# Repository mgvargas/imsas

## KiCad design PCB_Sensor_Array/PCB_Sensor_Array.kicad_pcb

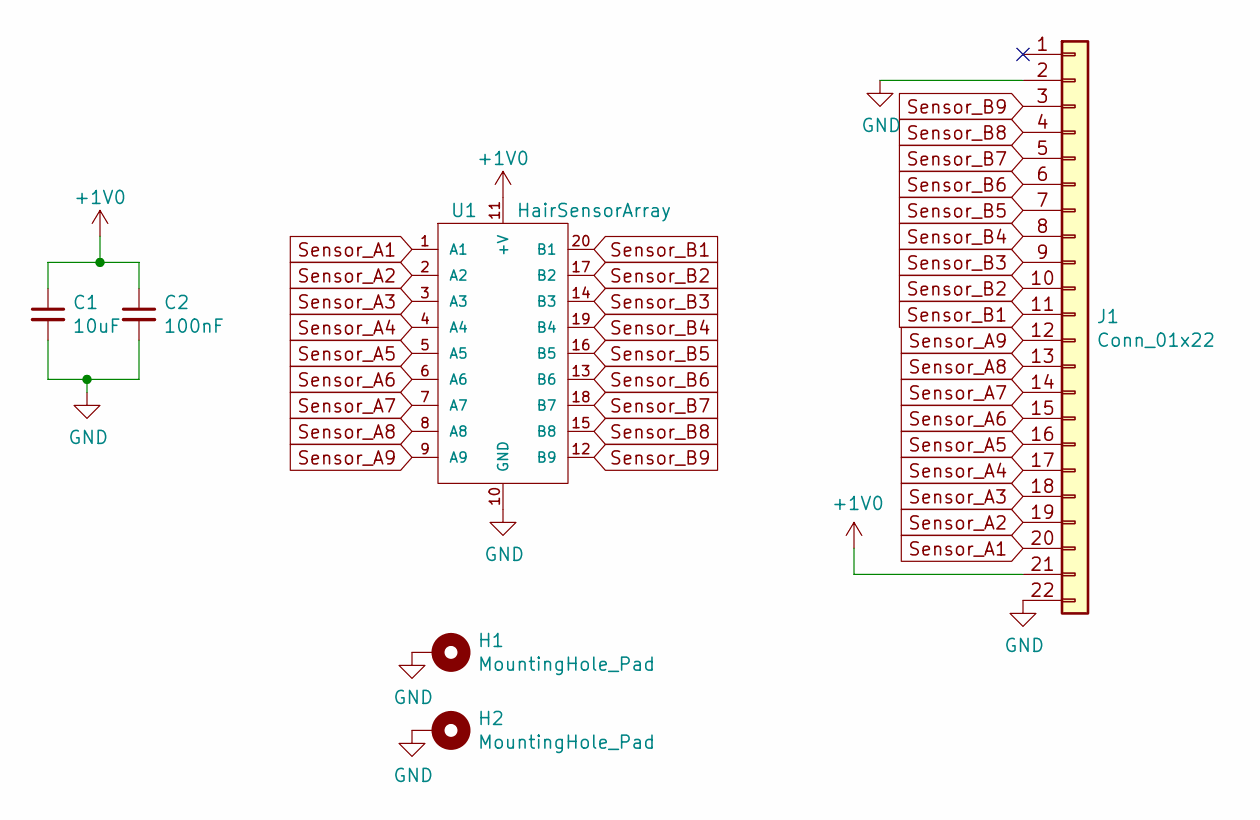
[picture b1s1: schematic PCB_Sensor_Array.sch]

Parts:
C1: 10uF; C_0603_1608Metric
C2: 100nF; C_0603_1608Metric
H1, H2: MountingHole_Pad; MountingHole_3.2mm_M3_Pad_Via
J1: Conn_01x22; Molex_200528-0220_1x22-1MP_P1.00mm_Horizontal
U1: HairSensorArray; Hair_Sensor_QFP-20_10x10_Pitch0.5mm

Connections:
+1V0: C1.1, C2.1, J1.21, U1.11 (+V)
GND: C1.2, C2.2, H1.1, H2.1, J1.2, J1.22, U1.10 (GND)
Sensor_A1: J1.20, U1.1 (A1)
Sensor_A2: J1.19, U1.2 (A2)
Sensor_A3: J1.18, U1.3 (A3)
Sensor_A4: J1.17, U1.4 (A4)
Sensor_A5: J1.16, U1.5 (A5)
Sensor_A6: J1.15, U1.6 (A6)
Sensor_A7: J1.14, U1.7 (A7)
Sensor_A8: J1.13, U1.8 (A8)
Sensor_A9: J1.12, U1.9 (A9)
Sensor_B1: J1.11, U1.20 (B1)
Sensor_B2: J1.10, U1.17 (B2)
Sensor_B3: J1.9, U1.14 (B3)
Sensor_B4: J1.8, U1.19 (B4)
Sensor_B5: J1.7, U1.16 (B5)
Sensor_B6: J1.6, U1.13 (B6)
Sensor_B7: J1.5, U1.18 (B7)
Sensor_B8: J1.4, U1.15 (B8)
Sensor_B9: J1.3, U1.12 (B9)

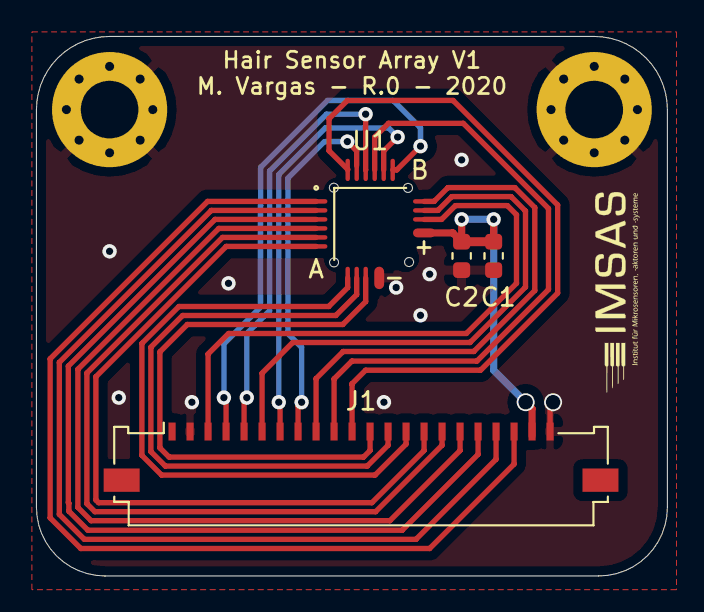
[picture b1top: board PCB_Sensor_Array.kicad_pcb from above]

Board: 2 copper layers, 35.1 x 30.0 mm, 6 parts (0 on the bottom side), 20 nets.

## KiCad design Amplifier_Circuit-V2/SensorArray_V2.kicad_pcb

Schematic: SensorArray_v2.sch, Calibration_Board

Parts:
C1: 10u; C_0805_2012Metric
C2, C3, C4, C5, C6, C7, C8, C9, C10: 100n; C_0402_1005Metric
C11, C12: 2.2u; C_0603_1608Metric
C13, C14: 12p; C_0402_1005Metric
D1, D6: LED; LED_0603_1608Metric
H1, H2, H3, H4: MountingHole_Pad; MountingHole_4.3mm_M4_Pad_Via
HSE1: 16MHz; Crystal_SMD_3225-4Pin_3.2x2.5mm
J1: UART_Connector; PinSocket_1x02_P2.54mm_Vertical
J2: Conn_02x05_Odd_Even; PinHeader_2x05_P1.27mm_Vertical_SMD
J3: I2C_Connector; PinHeader_1x02_P2.54mm_Vertical
J4: VCC_Connector; PinHeader_1x02_P2.54mm_Vertical
J5: SPI1_Connector; PinHeader_1x04_P2.54mm_Vertical
J6: 3V3_Connector; PinHeader_1x02_P2.54mm_Vertical
J10: SPI2_Connector; PinHeader_1x04_P2.54mm_Vertical
J11: USB_B_Micro; USB_Micro-B_Molex-105133-0001
R1, R2, R6, R19: 2k2; R_0603_1608Metric
R3, R4: 10k; R_0603_1608Metric
R5: 220; R_0603_1608Metric
R20: 1.5k; R_0603_1608Metric
S1: 1825910-6; SMD-4_5x4.4mm_P4mm; MPN 1825910-6; Digi-Key_PN 450-1650-ND
SW1: SW_DIP_x01; SW_DIP_SPSTx01_Slide_9.78x4.72mm_W7.62mm_P2.54mm
U1: STM32F405RGTx; LQFP-64_10x10mm_P0.5mm
U11: USBLC6-2SC6; SOT-23-6

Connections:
+3.3VA: U1.13 (VDDA); also elsewhere on the board
+3V3: C1.1, C2.1, C3.1, C4.1, C5.1, C6.1, C7.1, C8.1, C9.1, C10.1, J2.1, J6.1, R1.2, R2.2, R19.2, R20.1, U1.1 (VBAT), U1.19 (VDD), U1.32 (VDD), U1.48 (VDD), U1.64 (VDD); also elsewhere on the board
ADC_SPI2_CS: J10.1, U1.17 (PA3); also elsewhere on the board
AMP_OUT_A: U1.15 (PA1); also elsewhere on the board
AMP_OUT_B: U1.16 (PA2); also elsewhere on the board
BOOT0: R3.1, U1.60 (BOOT0)
BOOT1: R4.1, U1.28 (PB2)
GND: C1.2, C2.2, C3.2, C4.2, C5.2, C6.2, C7.2, C8.2, C9.2, C10.2, C11.2, C12.2, C13.2, C14.2, H1.1, H2.1, H3.1, H4.1, HSE1.2, HSE1.4, J2.3, J2.5, J2.9, J4.2, J6.2, J11.5, R3.2, R4.2, R6.1, SW1.1, U1.18 (VSS), U1.63 (VSS), U11.2; also elsewhere on the board
GNDA: U1.12 (VSSA); also elsewhere on the board
HSE_IN: C13.1, HSE1.1, U1.5 (PH0)
HSE_OUT: R5.1, U1.6 (PH1)
I2C1_SCL: J3.2, R1.1, U1.58 (PB6)
I2C1_SDA: J3.1, R2.1, U1.59 (PB7)
MUXA_S0: U1.8 (PC0); also elsewhere on the board
MUXA_S1: U1.9 (PC1); also elsewhere on the board
MUXA_S2: U1.10 (PC2); also elsewhere on the board
MUXA_S3: U1.11 (PC3); also elsewhere on the board
MUXB_S0: U1.24 (PC4); also elsewhere on the board
MUXB_S1: U1.25 (PC5); also elsewhere on the board
MUXB_S2: U1.37 (PC6); also elsewhere on the board
MUXB_S3: U1.38 (PC7); also elsewhere on the board
NRST: J2.10, U1.7 (NRST)
unnamed: C11.1, U1.31 (VCAP_1)
unnamed: C12.1, U1.47 (VCAP_2)
unnamed: C14.1, HSE1.3, R5.2
unnamed: D1.1 (K), R6.2
unnamed: D1.2 (A), U1.33 (PB12)
unnamed: D6.2 (A), R20.2
PushButton_Calibration: S1.3, U1.39 (PC8)
PushButton_VDD: R19.1, S1.1
SPI1_CS: J5.1, U1.20 (PA4)
SPI1_CS_POTIA: U1.26 (PB0); also elsewhere on the board
SPI1_CS_POTIB: U1.27 (PB1); also elsewhere on the board
SPI1_MISO: J5.3, U1.22 (PA6); also elsewhere on the board
SPI1_MOSI: J5.4, U1.23 (PA7); also elsewhere on the board
SPI1_SCK: J5.2, U1.21 (PA5); also elsewhere on the board
SPI2_MISO: J10.3, U1.35 (PB14); also elsewhere on the board
SPI2_MOSI: J10.4, U1.36 (PB15); also elsewhere on the board
SPI2_SCK: J10.2, U1.29 (PB10); also elsewhere on the board
SWCLK: J2.4, U1.49 (PA14)
SWDIO: J2.2, U1.46 (PA13)
SWO: J2.6, U1.55 (PB3)
Switch_Mode: D6.1 (K), SW1.2, U1.40 (PC9)
USART1_RX: J1.2, U1.43 (PA10)
USART1_TX: J1.1, U1.42 (PA9)
USB_CONN_D+: J11.3, U11.3
USB_CONN_D-: J11.2, U11.1
USB_D+: U1.45 (PA12), U11.4
USB_D-: U1.44 (PA11), U11.6

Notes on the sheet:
Cl = 2x (CLoad_CRYSTAL - CPARASITIC) Cl = 2 x (9p - 3p)
I2C Pull resistors
Crystal
USB with ESD protection

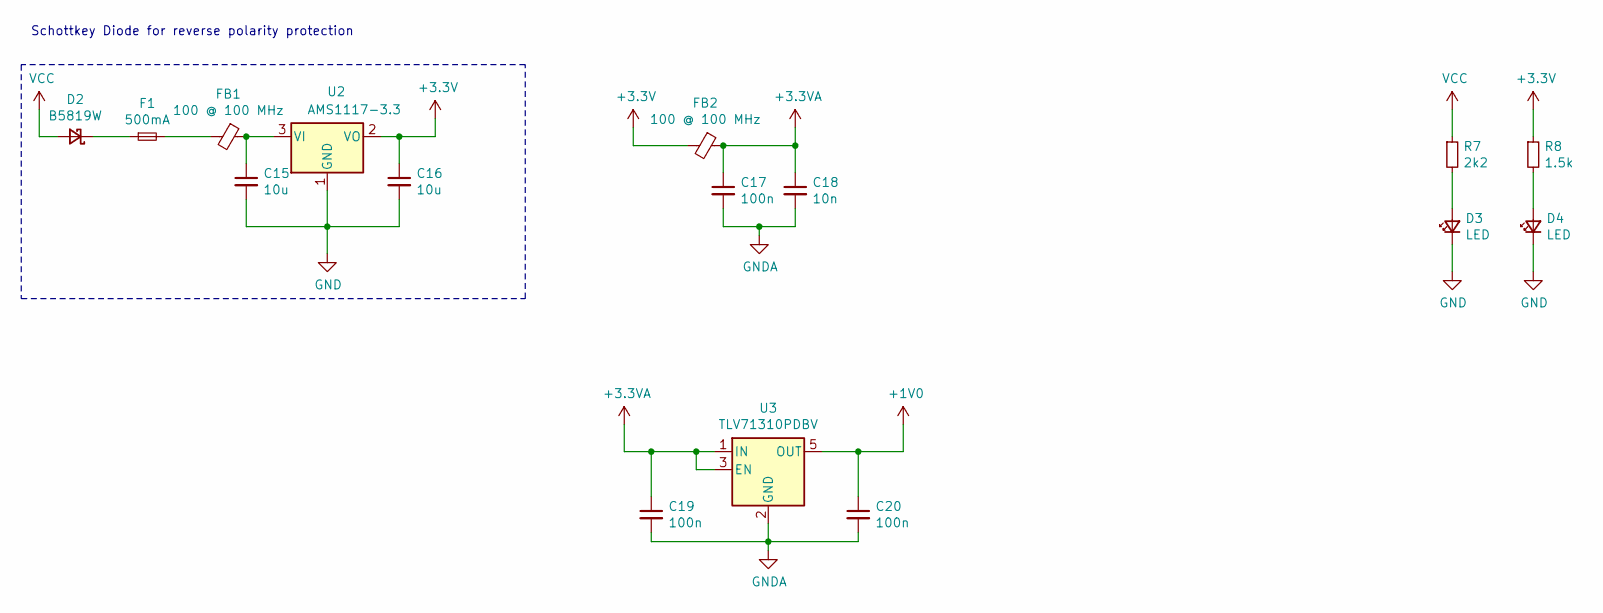
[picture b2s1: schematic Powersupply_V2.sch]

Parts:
C15, C16: 10u; C_0805_2012Metric
C17, C19, C20: 100n; C_0402_1005Metric
C18: 10n; C_0402_1005Metric
D2: B5819W; D_SOD-123
D3, D4: LED; LED_0603_1608Metric
F1: 500mA; Fuse_0603_1608Metric
FB1, FB2: 100 @ 100 MHz; L_0805_2012Metric
R7: 2k2; R_0603_1608Metric
R8: 1.5k; R_0603_1608Metric
U2: AMS1117-3.3; SOT-223-3_TabPin2
U3: TLV71310PDBV; SOT-23-5

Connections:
+1V0: C20.1, U3.5 (OUT); also elsewhere on the board
+3.3VA: C17.1, C18.1, C19.1, FB2.1, U3.1 (IN), U3.3 (EN); also elsewhere on the board
+3V3: C16.1, FB2.2, R8.1, U2.2 (VO); also elsewhere on the board
GND: C15.2, C16.2, D3.1 (K), D4.1 (K), U2.1 (GND); also elsewhere on the board
GNDA: C17.2, C18.2, C19.2, C20.2, U3.2 (GND); also elsewhere on the board
unnamed: C15.1, FB1.1, U2.3 (VI)
unnamed: D3.2 (A), R7.2
unnamed: D4.2 (A), R8.2

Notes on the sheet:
Schottkey Diode for reverse polarity protection

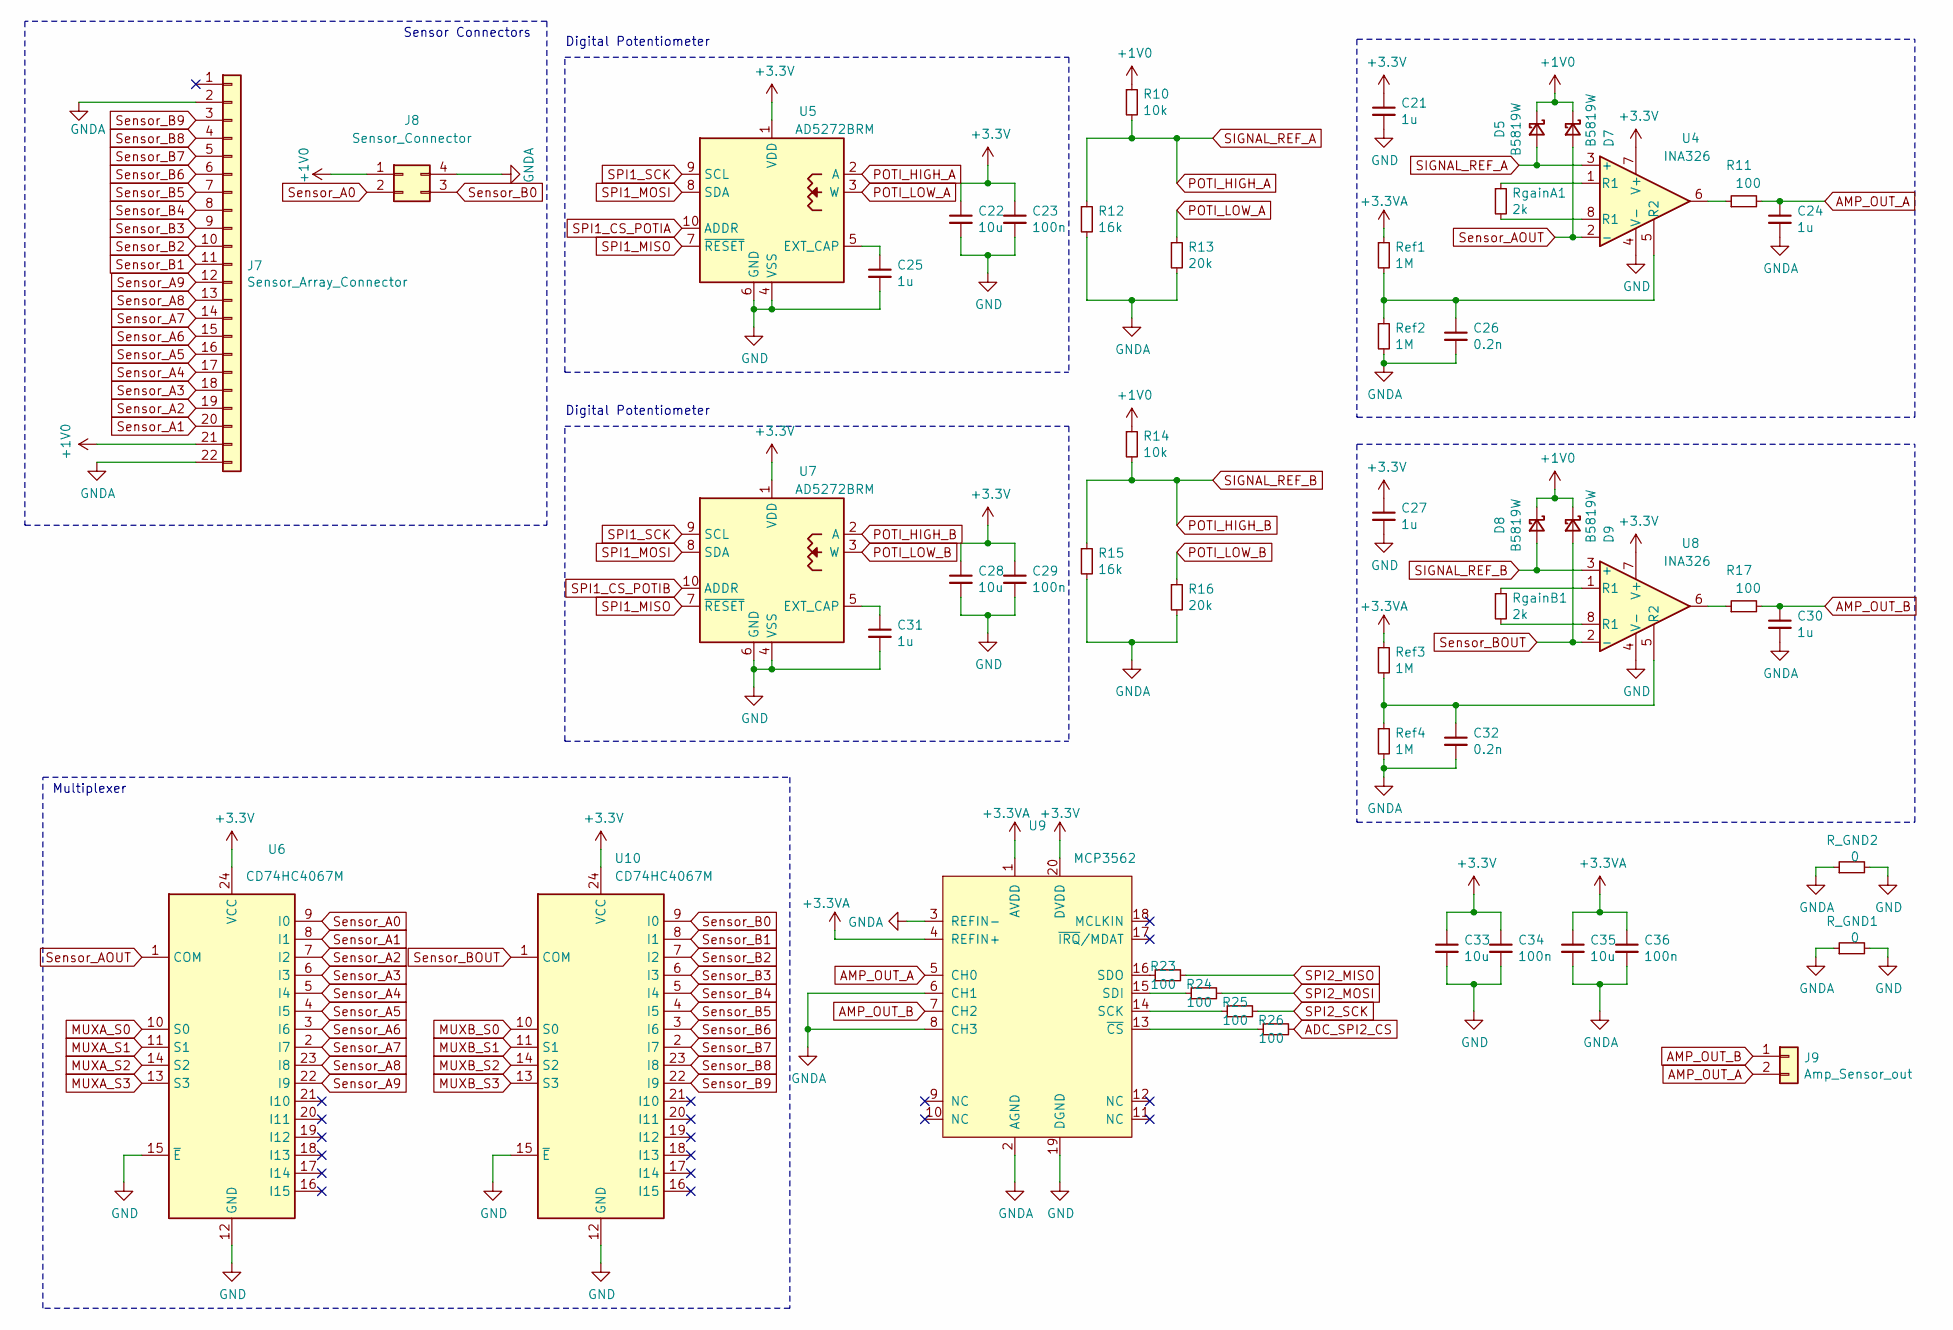
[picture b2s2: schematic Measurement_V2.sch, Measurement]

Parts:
C21, C24, C25, C27, C30, C31: 1u; C_0603_1608Metric
C22, C28, C33, C35: 10u; C_0805_2012Metric
C23, C29, C34, C36: 100n; C_0402_1005Metric
C26, C32: 0.2n; C_0603_1608Metric
D5, D7, D8, D9: B5819W; D_SOD-123
J7: Sensor_Array_Connector; Molex_200528-0220_1x22-1MP_P1.00mm_Horizontal
J8: Sensor_Connector; PinHeader_2x02_P2.54mm_Vertical
J9: Amp_Sensor_out; PinHeader_1x02_P2.54mm_Vertical
R10, R14: 10k; R_0603_1608Metric
R11, R17: 100; R_0603_1608Metric
R12, R15: 16k; R_0603_1608Metric
R13, R16: 20k; R_0603_1608Metric
R23, R24, R25, R26: 100; R_0402_1005Metric
R_GND1, R_GND2: 0; R_0603_1608Metric
Ref1, Ref2, Ref3, Ref4: 1M; R_0603_1608Metric
RgainA1: 2k; R_0603_1608Metric
RgainB1: 2k; R_0603_1608Metric
U4, U8: INA326; MSOP-8_3x3mm_P0.65mm
U5, U7: AD5272BRM; MSOP-10_3x3mm_P0.5mm
U6, U10: CD74HC4067M; SOIC-24W_7.5x15.4mm_P1.27mm
U9: MCP3562; TSSOP-20_W4.4mm

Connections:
+1V0: D5.1 (K), D7.1 (K), D8.1 (K), D9.1 (K), J7.21, J8.1, R10.1, R14.1; also elsewhere on the board
+3.3VA: C35.1, C36.1, Ref1.1, Ref3.1, U9.1 (AVDD), U9.4 (REFIN+); also elsewhere on the board
+3V3: C21.1, C22.1, C23.1, C27.1, C28.1, C29.1, C33.1, C34.1, U4.7 (V+), U5.1 (VDD), U6.24 (VCC), U7.1 (VDD), U8.7 (V+), U9.20 (DVDD), U10.24 (VCC); also elsewhere on the board
ADC_SPI2_CS: R26.2; also elsewhere on the board
AMP_OUT_A: C24.1, J9.2, R11.2, U9.5 (CH0); also elsewhere on the board
AMP_OUT_B: C30.1, J9.1, R17.2, U9.7 (CH2); also elsewhere on the board
GND: C21.2, C22.2, C23.2, C25.2, C27.2, C28.2, C29.2, C31.2, C33.2, C34.2, R_GND1.2, R_GND2.2, U4.4 (V-), U5.4 (VSS), U5.6 (GND), U6.12 (GND), U6.15 (~E), U7.4 (VSS), U7.6 (GND), U8.4 (V-), U9.19 (DGND), U10.12 (GND), U10.15 (~E); also elsewhere on the board
GNDA: C24.2, C26.2, C30.2, C32.2, C35.2, C36.2, J7.2, J7.22, J8.4, R12.2, R13.2, R15.2, R16.2, R_GND1.1, R_GND2.1, Ref2.2, Ref4.2, U9.2 (AGND), U9.3 (REFIN-), U9.6 (CH1), U9.8 (CH3); also elsewhere on the board
MUXA_S0: U6.10 (S0); also elsewhere on the board
MUXA_S1: U6.11 (S1); also elsewhere on the board
MUXA_S2: U6.14 (S2); also elsewhere on the board
MUXA_S3: U6.13 (S3); also elsewhere on the board
MUXB_S0: U10.10 (S0); also elsewhere on the board
MUXB_S1: U10.11 (S1); also elsewhere on the board
MUXB_S2: U10.14 (S2); also elsewhere on the board
MUXB_S3: U10.13 (S3); also elsewhere on the board
unnamed: C25.1, U5.5 (EXT_CAP)
unnamed: C26.1, Ref1.2, Ref2.1, U4.5 (R2)
unnamed: C31.1, U7.5 (EXT_CAP)
unnamed: C32.1, Ref3.2, Ref4.1, U8.5 (R2)
unnamed: R11.1, U4.6
unnamed: R17.1, U8.6
unnamed: R23.1, U9.16 (SDO)
unnamed: R24.1, U9.15 (SDI)
unnamed: R25.1, U9.14 (SCK)
unnamed: R26.1, U9.13 (~CS~)
unnamed: RgainA1.1, U4.1 (R1)
unnamed: RgainA1.2, U4.8 (R1)
unnamed: RgainB1.1, U8.1 (R1)
unnamed: RgainB1.2, U8.8 (R1)
POTI_HIGH_A: D5.2 (A), R10.2, R12.1, U4.3 (+), U5.2 (A)
POTI_HIGH_B: D8.2 (A), R14.2, R15.1, U7.2 (A), U8.3 (+)
POTI_LOW_A: R13.1, U5.3 (W)
POTI_LOW_B: R16.1, U7.3 (W)
SPI1_CS_POTIA: U5.10 (ADDR); also elsewhere on the board
SPI1_CS_POTIB: U7.10 (ADDR); also elsewhere on the board
SPI1_MISO: U5.7 (~RESET), U7.7 (~RESET); also elsewhere on the board
SPI1_MOSI: U5.8 (SDA), U7.8 (SDA); also elsewhere on the board
SPI1_SCK: U5.9 (SCL), U7.9 (SCL); also elsewhere on the board
SPI2_MISO: R23.2; also elsewhere on the board
SPI2_MOSI: R24.2; also elsewhere on the board
SPI2_SCK: R25.2; also elsewhere on the board
Sensor_A0: J8.2, U6.9 (I0)
Sensor_A1: J7.20, U6.8 (I1)
Sensor_A2: J7.19, U6.7 (I2)
Sensor_A3: J7.18, U6.6 (I3)
Sensor_A4: J7.17, U6.5 (I4)
Sensor_A5: J7.16, U6.4 (I5)
Sensor_A6: J7.15, U6.3 (I6)
Sensor_A7: J7.14, U6.2 (I7)
Sensor_A8: J7.13, U6.23 (I8)
Sensor_A9: J7.12, U6.22 (I9)
Sensor_AOUT: D7.2 (A), U4.2 (-), U6.1 (COM)
Sensor_B0: J8.3, U10.9 (I0)
Sensor_B1: J7.11, U10.8 (I1)
Sensor_B2: J7.10, U10.7 (I2)
Sensor_B3: J7.9, U10.6 (I3)
Sensor_B4: J7.8, U10.5 (I4)
Sensor_B5: J7.7, U10.4 (I5)
Sensor_B6: J7.6, U10.3 (I6)
Sensor_B7: J7.5, U10.2 (I7)
Sensor_B8: J7.4, U10.23 (I8)
Sensor_B9: J7.3, U10.22 (I9)
Sensor_BOUT: D9.2 (A), U8.2 (-), U10.1 (COM)

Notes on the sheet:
Digital Potentiometer
Sensor Connectors
Multiplexer

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
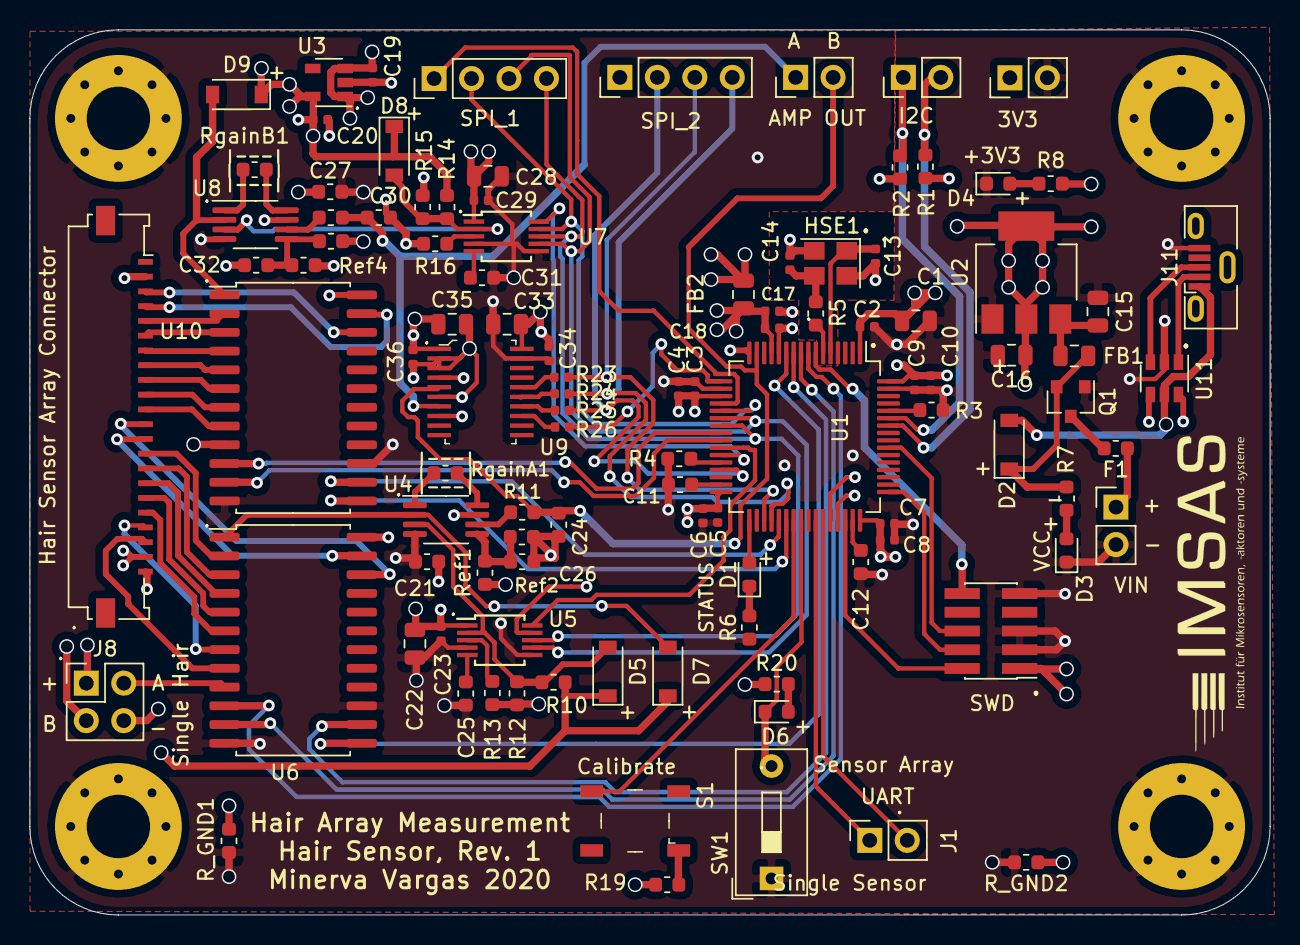
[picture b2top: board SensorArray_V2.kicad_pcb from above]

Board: 4 copper layers, 84.1 x 60.0 mm, 108 parts (0 on the bottom side), 97 nets.

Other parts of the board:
Q1: AO3401A; SOT-23

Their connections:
GND: Q1.1; also elsewhere on the board

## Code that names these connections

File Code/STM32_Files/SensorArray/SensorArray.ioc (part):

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Mcu.Name=STM32F405RGTx
Mcu.Package=LQFP64
Mcu.UserName=STM32F405RGTx
PA1.GPIOParameters=GPIO_Label
PA1.GPIO_Label=ADC_Amplifier_A
PA1.Signal=ADCx_IN1
PA10.Mode=Asynchronous
PA10.Signal=USART1_RX
PA11.GPIOParameters=GPIO_Speed,GPIO_PuPd,GPIO_Mode
PA11.GPIO_Mode=GPIO_MODE_AF_PP
PA11.GPIO_PuPd=GPIO_NOPULL
PA11.GPIO_Speed=GPIO_SPEED_FREQ_VERY_HIGH
PA11.Mode=Device_Only
PA11.Signal=USB_OTG_FS_DM
PA12.GPIOParameters=GPIO_Speed,GPIO_PuPd,GPIO_Mode
PA12.GPIO_Mode=GPIO_MODE_AF_PP
PA12.GPIO_PuPd=GPIO_NOPULL
PA12.GPIO_Speed=GPIO_SPEED_FREQ_VERY_HIGH
PA12.Mode=Device_Only
PA12.Signal=USB_OTG_FS_DP
PA13.Mode=Trace_Asynchronous_SW
PA13.Signal=SYS_JTMS-SWDIO
PA14.Mode=Trace_Asynchronous_SW
PA14.Signal=SYS_JTCK-SWCLK
PA2.GPIOParameters=GPIO_Label
PA2.GPIO_Label=ADC_Amplifier_B
PA2.Signal=ADCx_IN2
PA3.GPIOParameters=GPIO_Label
PA3.GPIO_Label=SPI2_CS_ADC
PA3.Signal=GPIO_Output
PA4.GPIOParameters=GPIO_Label
PA4.GPIO_Label=SPI1_CS
PA4.Signal=GPIO_Output
PA5.GPIOParameters=GPIO_PuPd
PA5.GPIO_PuPd=GPIO_PULLDOWN
PA5.Mode=Full_Duplex_Master
PA5.Signal=SPI1_SCK
PA6.GPIOParameters=GPIO_PuPd
PA6.GPIO_PuPd=GPIO_PULLUP
PA6.Mode=Full_Duplex_Master
PA6.Signal=SPI1_MISO
PA7.Mode=Full_Duplex_Master
PA7.Signal=SPI1_MOSI
PA9.Mode=Asynchronous
PA9.Signal=USART1_TX
PB0.GPIOParameters=GPIO_Label
PB0.GPIO_Label=SPI1_CS_POTIA
PB0.Signal=GPIO_Output
PB1.GPIOParameters=GPIO_Label
PB1.GPIO_Label=SPI1_CS_POTIB
PB1.Signal=GPIO_Output
PB10.GPIOParameters=GPIO_PuPd
PB10.GPIO_PuPd=GPIO_NOPULL
PB10.Mode=Full_Duplex_Master
PB10.Signal=SPI2_SCK
PB12.GPIOParameters=GPIO_Label
PB12.GPIO_Label=LED_STATUS
PB12.Signal=GPIO_Output
PB14.Mode=Full_Duplex_Master
PB14.Signal=SPI2_MISO
PB15.Mode=Full_Duplex_Master
PB15.Signal=SPI2_MOSI
PB3.Mode=Trace_Asynchronous_SW
PB3.Signal=SYS_JTDO-SWO
PB6.Mode=I2C
PB6.Signal=I2C1_SCL
PB7.Mode=I2C
PB7.Signal=I2C1_SDA
PC0.GPIOParameters=PinState,GPIO_Label
PC0.GPIO_Label=MUXA_S0
PC0.PinState=GPIO_PIN_RESET
PC0.Signal=GPIO_Output
PC1.GPIOParameters=GPIO_Label
PC1.GPIO_Label=MUXA_S1
PC1.Signal=GPIO_Output
PC2.GPIOParameters=GPIO_Label
PC2.GPIO_Label=MUXA_S2
PC2.Signal=GPIO_Output
PC3.GPIOParameters=GPIO_Label
PC3.GPIO_Label=MUXA_S3
PC3.Signal=GPIO_Output
PC4.GPIOParameters=GPIO_Label
PC4.GPIO_Label=MUXB_S0
PC4.Signal=GPIO_Output
PC5.GPIOParameters=GPIO_Label
PC5.GPIO_Label=MUXB_S1
PC5.Signal=GPIO_Output
PC6.GPIOParameters=GPIO_Label
PC6.GPIO_Label=MUXB_S2
PC6.Signal=GPIO_Output
PC7.GPIOParameters=GPIO_Label
PC7.GPIO_Label=MUXB_S3
PC7.Signal=GPIO_Output
PC8.GPIOParameters=GPIO_Label
PC8.GPIO_Label=PushButton_Calibration
PC8.Signal=GPIO_Input
PC9.GPIOParameters=GPIO_Label
PC9.GPIO_Label=Switch_Mode
PC9.Signal=GPIO_Input
PH0-OSC_IN.Mode=HSE-External-Oscillator
PH0-OSC_IN.Signal=RCC_OSC_IN
PH1-OSC_OUT.Mode=HSE-External-Oscillator
PH1-OSC_OUT.Signal=RCC_OSC_OUT
RCC.HSE_VALUE=16000000
RCC.SYSCLKFreq_VALUE=168000000
RCC.SYSCLKSource=RCC_SYSCLKSOURCE_PLLCLK
board=custom

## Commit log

2020-06-29 V1
    Amplifier circuit for the hair sensor array, select between 9 sensors or
    1
2020-06-29 Add BOM and other component lists
2020-06-29 Add IMSAS logo to board
2020-08-29 Blink a led
2020-09-03 Working Mux
2020-09-03 Adding code
2020-09-11 Clean repo, add gitignore
2020-09-11 Cleaning repo
2020-09-18 Half working digital potentiometer
2020-09-27 Start code for the ADC and clean repo
2020-09-27 Correcting GPIO port for the ADC
2020-09-29 Digital Potentiometer working (set value)
2020-09-30 Updated schematic
2020-09-30 Matlab code for calculating resistance/voltage
2020-10-06 Configuring ADC, working
2020-10-09 V2 of the PCB, corrected SPI, connector and added safety diodes
2020-10-30 General code structure. SPI communication not working
2020-11-03 Calculating Dig.Poti resolution
2020-11-30 Clean repo, remove duplicated .ioc files
2020-11-30 Add .ioc config file for the second version of the board
2020-11-30 Sent to fabrication
2020-12-07 Add PCB for sensor array chip, V1
2020-12-07 Adjust hole size (4mm -> 4.2mm)
2021-01-04 Solve debug problems
2021-01-05 Add ADC datasheet, update MX file for second board version
2021-01-11 Working with CubeIDE 5.0. SPI1 and 2 configured for V2. USB configured but half working. Recognized but no connection to Hterm.
2021-01-13 GUI Folder
2021-01-13 Create folder for interface of the board with the PC
2021-01-17 USB communication working. Changed Debug configuration to STLinkGDB server
2021-01-19 Fixing USB communication bug, now it is always recognized. Lowering CLK freq to 84MHz, I have to test if 164HZ also work
2021-01-20 Increasing clock frequency to 168MHz
2021-01-20 Updated Working GUI
2021-01-20 Start to comment and clean the code
2021-01-23 Added Functionality
2021-01-23 Added GUI Functionality
2021-01-25 Removing warnings, reading ADC, but it does not always work
2021-01-25 ADC working, sends value over USB
2021-01-27 Removing scan register configuration for teh ADC, delete later
2021-01-28 Added some datasheets and logos for the PCB
2021-01-29 Updated GUI
2021-01-30 Test sending ADC values to GUI
2021-01-30 Calibrating and reading single sensor, sending over USB
2021-01-31 Changed Line Chart to Spline, added IMSAS Icon
2021-01-31 Splitting main.c in several files: ADC, calibration, Potentiometer, multiplexor. Reads and calibrates 1 sensor
2021-01-31 Commands can be send via USB in format #cmd:arg1,arg2
2021-02-01 Change MISO of Poti to Pull-up state, now Potis work stable
2021-02-01 Sending hspi as parameter for the Poti_SPI_init function
2021-02-04 Added CSV Button Option
2021-02-11 Removed Exceptions
2021-02-19 Reading sensor array and sending the values as float array
2021-02-19 Speeding up the code, now array data is sent every 25us. The command #get_poti:1,2 works now
2021-02-22 Correcting calibration, works for sensors without hairs. Reducing oversampling rate for ADC.
2021-02-22 Reducing pause for Mux. Measures both arrays in 70ms.
2021-02-24 Increased Serial Recording
2021-02-27 Send Data Command
2021-03-01 Updated Time Column
2021-03-10 Update Matlab code to calculate needed resistance
2021-06-25 Modified Timers
2021-07-05 Speed Up the Application
2021-07-06 no changes, just to update
2021-07-14 Activating calibration button. Error in PCB detected, the button is not grounded, but it kinda works.
2021-07-14 Add milling file for the PCB (CNC machine, AVT 0)
2021-07-18 Comments Added
2021-07-18 Added Comments
